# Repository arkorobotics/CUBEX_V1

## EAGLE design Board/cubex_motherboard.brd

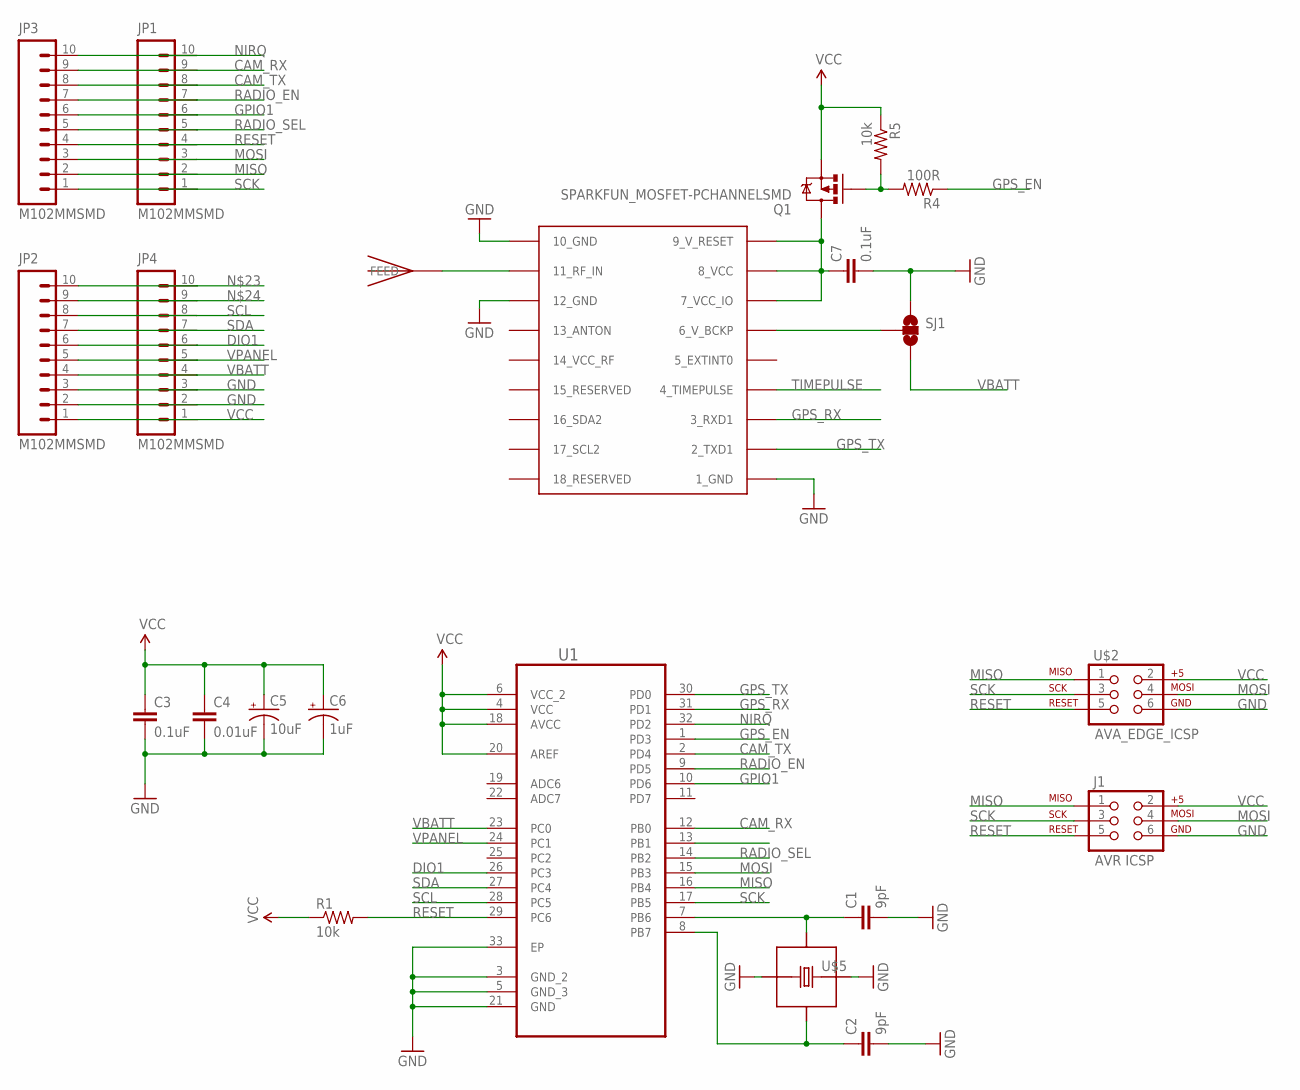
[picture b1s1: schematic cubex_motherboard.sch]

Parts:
C1, C2: 9pF; 0805
C3: 0.1uF; 0805
C4: 0.01uF; 0805
C5: 10uF; EIA3216
C6: 1uF; EIA3216
C7: 0.1uF; SPARKFUN_0805
J1: AVR ICSP; SPARKFUN_2X3-NS
JP1, JP2, JP3, JP4: M102MMSMD; 1X10-2MM-SMD
Q1: SPARKFUN_MOSFET-PCHANNELSMD; SPARKFUN_SOT23-3
R1: 10k; 0805
R4: 100R; SPARKFUN_0805
R5: 10k; SPARKFUN_0805
SJ1: SPARKFUN_SOLDERJUMPER_2WAYT; SPARKFUN_SJ_2
U1: AVA_ATMEGA328P-MU; AVA_QFN50P500X500X100-33N
U$2: AVA_EDGE_ICSP; AVA_EDGE_MOUNTED_ICSP
U$3: AVA_JTI_ANTENNA-1575AT43A40
U$4: AVA_UBLOX_MAX-6
U$5: AVA_EPSON_FA-20H_CRYSTAL; AVA_EPSON-FA-20H-CRYSTAL

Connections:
CAM_RX: JP1.9, JP3.9, U1.12 (PB0)
CAM_TX: JP1.8, JP3.8, U1.2 (PD4)
DIO1: JP2.6, JP4.6, U1.26 (PC3)
GND: C1.2, C2.2, C3.2, C4.2, C5.C (-), C6.C (-), C7.2, J1.6, JP2.2, JP2.3, JP4.2, JP4.3, SJ1.1, U1.3 (GND_2), U1.5 (GND_3), U1.21 (GND), U1.33 (EP), U$2.6, U$4.1_GND, U$4.10_GND, U$4.12_GND, U$5.1, U$5.3
GPIO1: JP1.6, JP3.6, U1.10 (PD6)
GPS_EN: R4.1, U1.1 (PD3)
GPS_RX: U1.31 (PD1), U$4.3_RXD1
GPS_TX: U1.30 (PD0), U$4.2_TXD1
MISO: J1.1, JP1.2, JP3.2, U1.16 (PB4), U$2.1
MOSI: J1.4, JP1.3, JP3.3, U1.15 (PB3), U$2.4
unnamed: C7.1, Q1.3 (D), U$4.7_VCC_IO, U$4.8_VCC, U$4.9_V_RESET
unnamed: SJ1.2, U$4.6_V_BCKP
unnamed: Q1.1 (G), R4.2, R5.2
unnamed: U$3.FEED, U$4.11_RF_IN
unnamed: C1.1, U1.7 (PB6), U$5.4
unnamed: C2.1, U1.8 (PB7), U$5.2
unnamed: JP2.10, JP4.10
unnamed: JP2.9, JP4.9
NIRQ: JP1.10, JP3.10, U1.32 (PD2)
RADIO_EN: JP1.7, JP3.7, U1.9 (PD5)
RADIO_SEL: JP1.5, JP3.5, U1.14 (PB2)
RESET: J1.5, JP1.4, JP3.4, R1.2, U1.29 (PC6), U$2.5
SCK: J1.3, JP1.1, JP3.1, U1.17 (PB5), U$2.3
SCL: JP2.8, JP4.8, U1.28 (PC5)
SDA: JP2.7, JP4.7, U1.27 (PC4)
TIMEPULSE: U$4.4_TIMEPULSE
VBATT: JP2.4, JP4.4, SJ1.3, U1.23 (PC0)
VCC: C3.1, C4.1, C5.A (+), C6.A (+), J1.2, JP2.1, JP4.1, Q1.2 (S), R1.1, R5.1, U1.4 (VCC), U1.6 (VCC_2), U1.18 (AVCC), U1.20 (AREF), U$2.2
VPANEL: JP2.5, JP4.5, U1.24 (PC1)

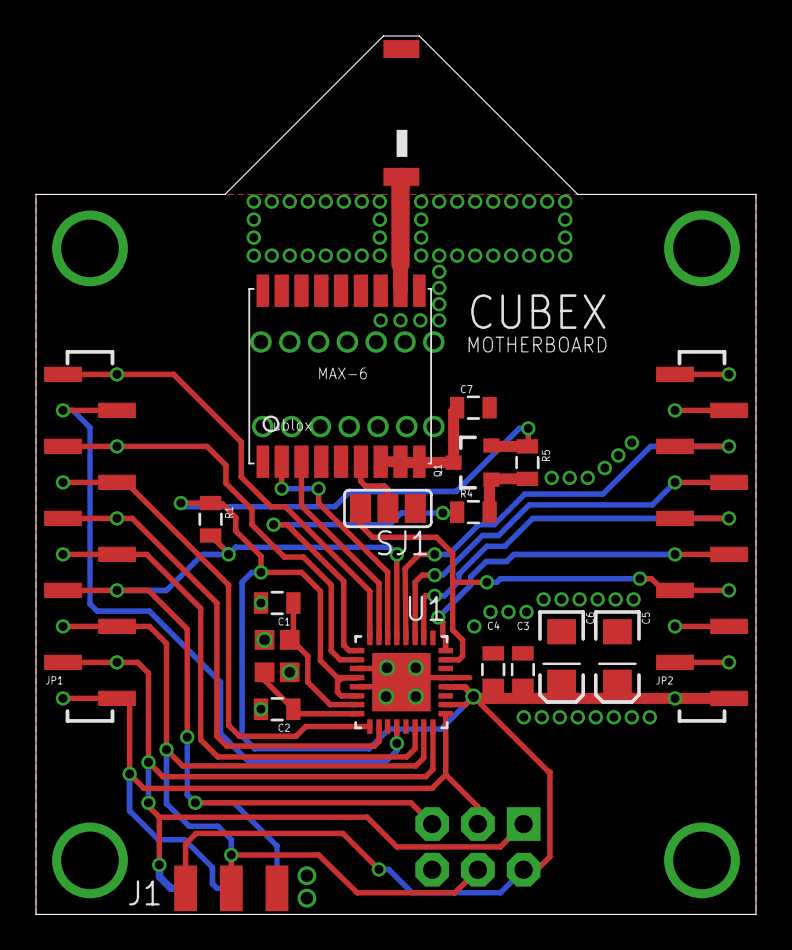
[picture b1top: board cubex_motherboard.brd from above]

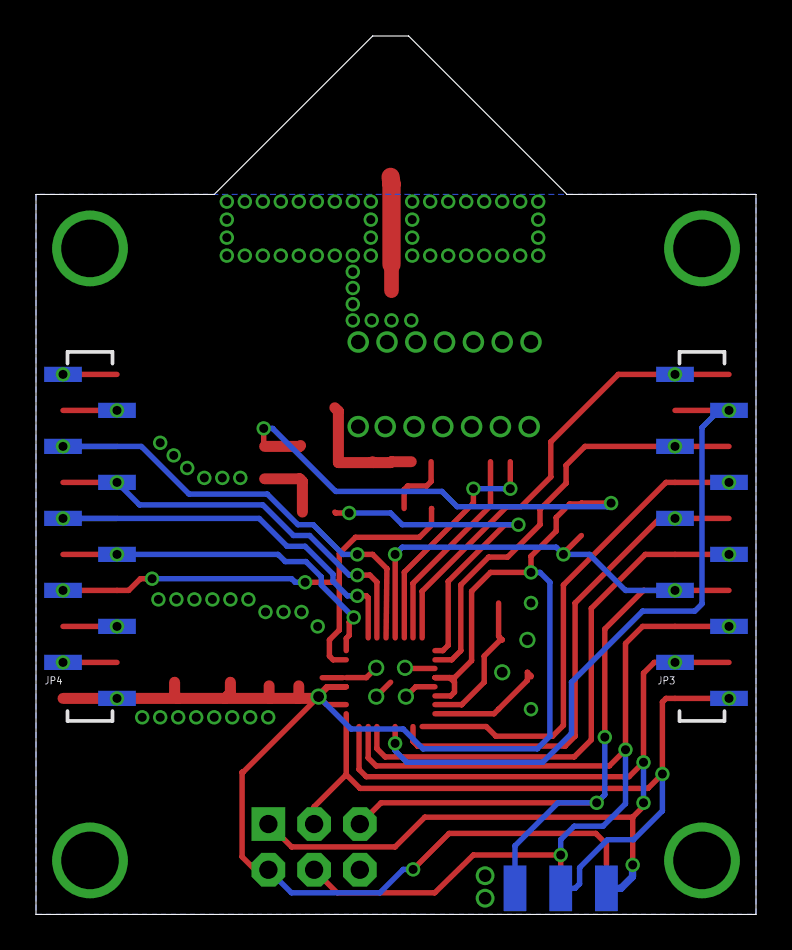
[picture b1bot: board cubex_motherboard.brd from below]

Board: 2 copper layers, 40.0 x 48.8 mm, 22 parts (2 on the bottom side), 28 nets.

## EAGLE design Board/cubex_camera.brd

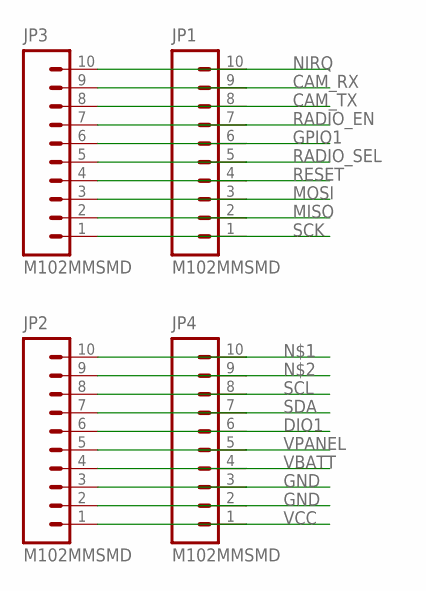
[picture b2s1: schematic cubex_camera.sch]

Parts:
JP1, JP2, JP3, JP4: M102MMSMD; 1X10-2MM-SMD

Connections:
CAM_RX: JP1.9, JP3.9
CAM_TX: JP1.8, JP3.8
DIO1: JP2.6, JP4.6
GND: JP2.2, JP2.3, JP4.2, JP4.3
GPIO1: JP1.6, JP3.6
MISO: JP1.2, JP3.2
MOSI: JP1.3, JP3.3
unnamed: JP2.10, JP4.10
unnamed: JP2.9, JP4.9
NIRQ: JP1.10, JP3.10
RADIO_EN: JP1.7, JP3.7
RADIO_SEL: JP1.5, JP3.5
RESET: JP1.4, JP3.4
SCK: JP1.1, JP3.1
SCL: JP2.8, JP4.8
SDA: JP2.7, JP4.7
VBATT: JP2.4, JP4.4
VCC: JP2.1, JP4.1
VPANEL: JP2.5, JP4.5

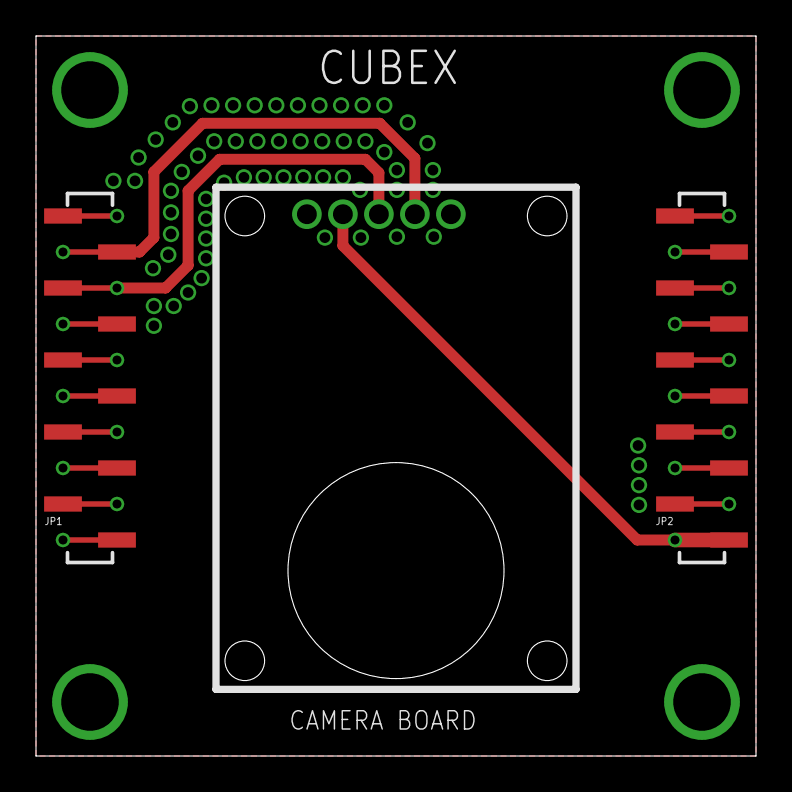
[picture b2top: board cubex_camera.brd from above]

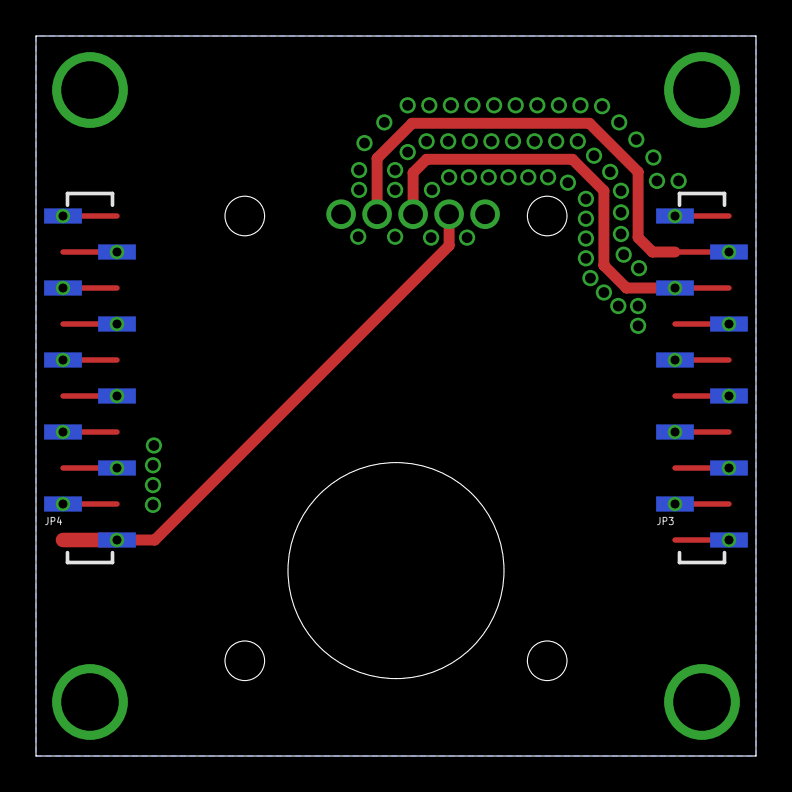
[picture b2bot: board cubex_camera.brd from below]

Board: 2 copper layers, 40.0 x 40.0 mm, 4 parts (2 on the bottom side), 19 nets.

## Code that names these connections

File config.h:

#ifndef __CONFIG_H__
#define __CONFIG_H__

#define RTTY_CALLSIGN "CUBEX1"

/* CONFIGURABLE BITS */
#define ASCII 8          // ASCII 7 or 8
#define STOPBITS 2       // Either 1 or 2
#define TXDELAY 0        // Delay between sentence TX's
#define RTTY_BAUD 300     // Baud rate for use with RFM22B Max = 600
//#define RADIO_FREQUENCY 434550 // 434.550 Reality 
#define RADIO_POWER  0x07
#define RADIO_REBOOT 20  // Reboot Radio every X telemetry lines
#define APRS_TX_INTERVAL  120000  // APRS TX Interval 

#define TX_DELAY      300   // default was 300


#define SI446x_SHUTDOWN_PIN   5
#define SI446x_GPIO_PIN       6
#define SI446x_NIRQ_PIN       2

#define VCXO_FREQ 26000000L

#define RADIO_FREQUENCY   434500000UL


#define GPS_ENABLE_PIN        3


#define STATUS_LED            7  // Not Connected on CUBEX


#define CAM_TX_PIN            4
#define CAM_RX_PIN            8


#define VBATT_PIN             A0
#define VPANEL_PIN            A1
#define DIO1_PIN              A3
#define SDA_PIN               A4
#define SCL_PIN               A5

#endif

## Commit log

2014-04-28 CUBEX_V1
    First Commit
2014-04-28 Added Adafruit VC0706 library
    Place this in the arduino libraries (THIS IS LIBRARY HAS BEEN MODIFIED)
2014-04-28 Push read-only data into PROGMEM
2014-05-01 Sending data, bad jpeg
    possible pointer problem
2014-05-01 Read output DHT table from progmem
2014-05-01 Stupid typo
2014-05-01 test
    test
2014-05-02 WORKING SSDV!!!
    WORKING SSDV!!!
2014-05-02 Reduced resolution and added gps back in
    GPS was added back in and the resolution was brought down as it takes
    forever to send a 640x480 image at 300baud. THIS IS WORKING!!!
2014-06-12 Fixed ssdv crash when camera doesnt respond
    - Fixed ssdv crash when camera doesnt respond
    - change frequency
2014-06-24 Added board/BOM
    Added board/BOM

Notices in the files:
parts and their libraries:
SparkFun: Licensing: CC v3.0 Share-Alike You are welcome to use this library for commercial purposes.
